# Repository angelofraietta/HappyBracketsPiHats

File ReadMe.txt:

Please quote for 100 units of these assembled.
The Bill of Materials is in the XML file

Note that the 2x20 Header is mounted on the bottom of the page, as shown in the images

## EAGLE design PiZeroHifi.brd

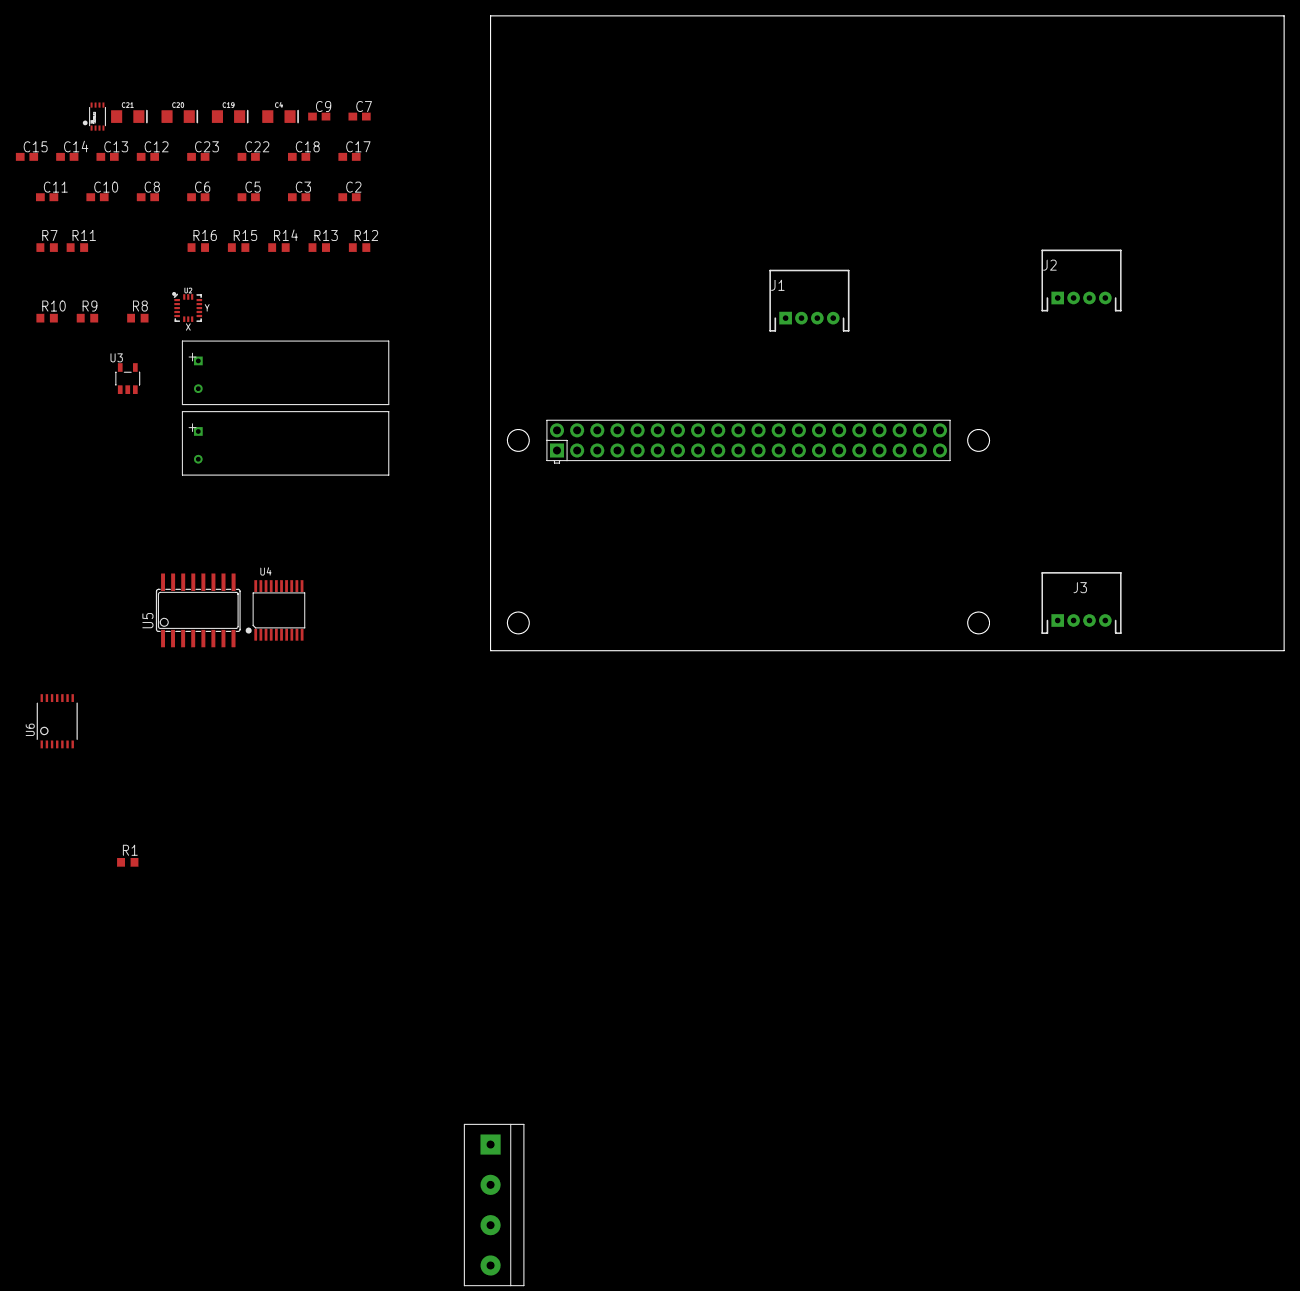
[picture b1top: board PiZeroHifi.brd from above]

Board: 2 copper layers, 100.0 x 80.0 mm, 45 parts (0 on the bottom side), 44 nets, no tracks yet.

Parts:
C1, C16: 1500uF; CAP8MMX3.5MMX20MM
C2, C10: 2.2nF; C0603
C3, C5, C11, C17, C18, C22, C23: 0.1uF; C0603
C4, C19, C20, C21: 10uF; EIA3216
C6, C8: 2.2uF; C0603
C7, C9, C13, C14, C15: 1uF; C0603
C12: 470p; C0603
CON1: RPI-ZEROPI-ZERO-THRUHOLE; RASPBERRYPI_ZERO_THRUHOLE
CON3: Audio Out; TERM-4P-SIDE-5.08MM
J1, J2, J3: GROVEGROVE-HORIZONTAL; JST-4-PTH
R1, R12, R13, R15: 10K; R0603
R7, R14, R16: 1K; R0603
R8, R9: 143K; R0603
R10, R11: 470; R0603
U1: TXS0102; VFSOP-8
U2: LSM6DS33; LGA-16-3X3
U3: TC1014-3.3V; GHI-IC_SOT23-5(MICROCHIP)
U4: PCM5101A; TSSOP20-0.65-6.5X4.4MM
U5: PAM8403; SOP-16
U6: TXB0104PWR; TSSOP14

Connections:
+3V3: C3.1, C17.2, C19.+, CON1.1, CON1.17, U1.P$3, U2.1, U2.4, U2.5, U2.16, U4.17, U4.20, U6.1
+5V: C1.P$1, C13.1, C14.1, C15.1, C16.P$1, CON1.2, CON1.4, J1.3, J2.3, J3.3, R16.2, U1.P$7, U3.1, U3.3, U5.4, U5.6, U5.13, U6.14
/MUTE: CON1.36, R12.2, R13.2
ACCEL_INT_1: CON1.11, U2.6
ACCEL_INT_2: CON1.13, U2.7
AN3V3: C4.+, C5.2, C21.+, C22.2, U3.5, U4.1, U4.8
GND: C1.P$2, C2.2, C3.2, C4.-, C5.1, C6.2, C10.2, C11.2, C12.1, C13.2, C14.2, C15.2, C16.P$2, C17.1, C18.2, C19.-, C20.-, C21.-, C22.1, C23.1, CON1.6, CON1.9, CON1.14, CON1.20, CON1.25, CON1.30, CON1.34, CON1.39, J1.4, J2.4, J3.4, R1.1, R7.2, R14.2, R15.1, U1.P$2, U2.8, U2.9, U2.10, U2.11, U2.12, U2.13, U2.15, U3.2, U4.3, U4.9, U4.10, U4.11, U4.12, U4.16, U4.19, U5.2, U5.9, U5.11, U5.15, U6.7
GPI022-OUT: J2.2, U6.11
GPIO21: CON1.29, U6.5
GPIO21-OUT: J2.1, U6.10
GPIO22: CON1.31, U6.4
GPIO23: CON1.33, U6.3
GPIO23-OUT: J1.1, U6.12
GPIO25: CON1.37, U6.2
GPIO25-OUT: J1.2, U6.13
unnamed: C8.1, U4.2
unnamed: C8.2, U4.4
unnamed: C6.1, U4.5
unnamed: C18.1, C20.+, U4.18
unnamed: R10.1, U4.6
unnamed: R11.1, U4.7
unnamed: C7.2, R8.1
unnamed: C9.1, C10.1, R11.2, R14.1
unnamed: C2.1, C7.1, R7.1, R10.2
unnamed: C9.2, R9.1
unnamed: R8.2, U5.7
unnamed: R9.2, U5.10
unnamed: C12.2, U3.4
unnamed: CON3.P$1, U5.1
unnamed: CON3.P$2, U5.3
unnamed: CON3.P$3, U5.14
unnamed: CON3.P$4, U5.16
unnamed: C11.1, U5.8
unnamed: R12.1, U5.12
unnamed: R13.1, U5.5
unnamed: C23.2, R15.2, R16.1, U1.P$6
OE: CON1.38, R1.2, U6.8
PCM_CLK: CON1.12, U4.13
PCM_DOUT: CON1.40, U4.14
PCM_FS: CON1.35, U4.15
SCL: CON1.5, U1.P$4, U2.2
SCL_OUT: J3.1, U1.P$1
SDA: CON1.3, U1.P$5, U2.3
SDA_OUT: J3.2, U1.P$8

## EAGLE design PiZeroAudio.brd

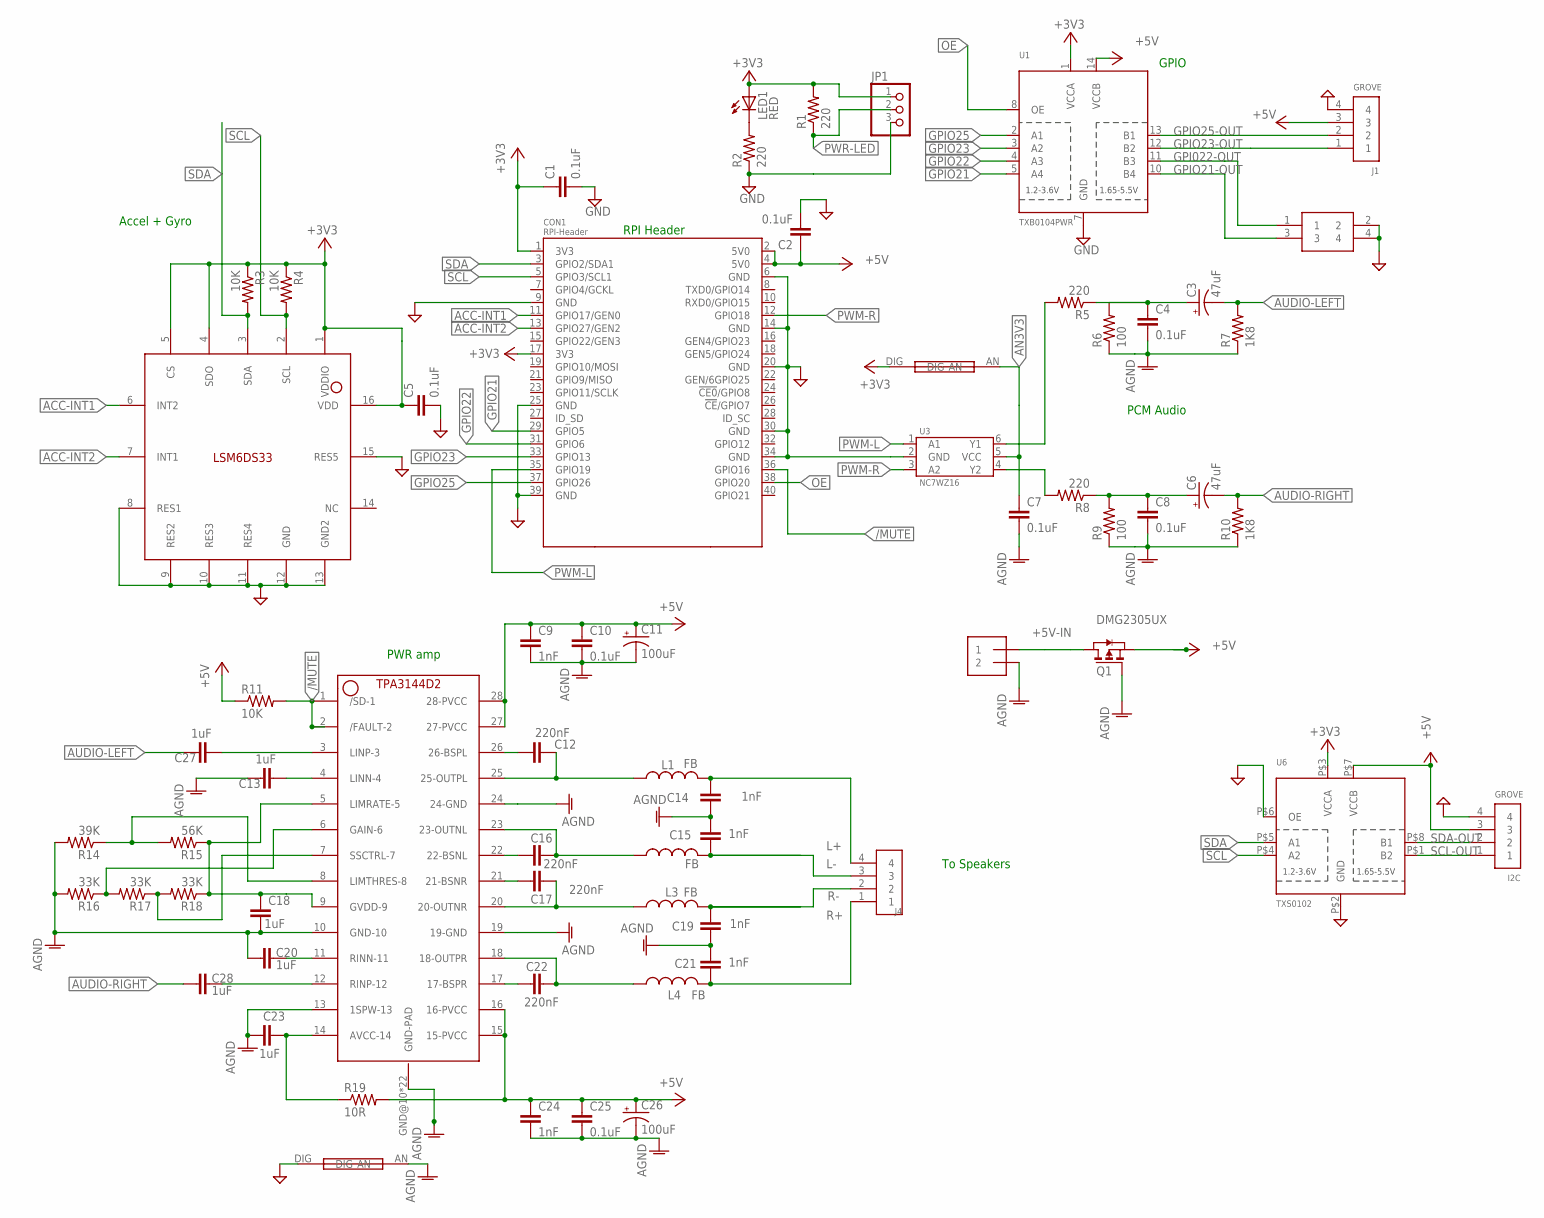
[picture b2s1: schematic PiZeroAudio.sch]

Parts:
C1, C2, C4, C5, C7, C8, C10, C25: 0.1uF; C0603
C3, C6: 47uF; EIA3216
C9, C14, C15, C19, C21, C24: 1nF; C0603
C11, C26: 100uF; EIA3216
C12, C16, C17, C22: 220nF; C0603
C13, C18, C20, C23, C27, C28: 1uF; C0603
CON1: RPI-Header; RASPBERRYPI_BASTELSTUBE_V13_RASPI_BOARD_B+_FULL
I2C: GROVE; JST-PH4
J1: GROVE; JST-PH4
J2: 2X2HEADER; 2X2
J3: 2X1-LOCKING; 22-23-2021
J4: 4X1-LOCKING; 22-23-2041
JP1: Header 1x3; 1X03
L1, L2, L3, L4: FB; L0806
LED1: RED; CHIP-LED0805
Q1: DMG2305UX; SOT23
R1, R2, R5, R8: 220; R0603
R3, R4, R11: 10K; R0603
R6, R9: 100; R0603
R7, R10: 1K8; R0603
R14: 39K; R0603
R15: 56K; R0603
R16, R17, R18: 33K; R0603
R19: 10R; R0603
SH1, SH2: SHORT
U1: TXB0104PWR; TSSOP14
U2: LSM6DS33; LGA-16-3X3
U3: NC7WZ16; SC-70-6
U5: TPA3144D2PWPR; HTSSOP28
U6: TXS0102; VFSOP-8

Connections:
+3V3: C1.1, C5.1, CON1.1 (3V3), CON1.17 (3V3), JP1.1, LED1.A, R1.2, R3.1, R4.1, SH1.DIG, U1.1 (VCCA), U2.1 (VDDIO), U2.4 (SDO), U2.5 (CS), U2.16 (VDD), U6.P$3 (VCCA)
+5V: C2.1, C9.1, C10.1, C11.+, C24.1, C25.1, C26.+, CON1.2 (5V0), CON1.4 (5V0), I2C.3, J1.3, Q1.S, R11.1, R19.2, U1.14 (VCCB), U5.15 (15-PVCC), U5.16 (16-PVCC), U5.27 (27-PVCC), U5.28 (28-PVCC), U6.P$7 (VCCB)
+5V-IN: J3.1, Q1.D
/MUTE: CON1.36 (GPIO16), R11.2, U5.1 (/SD-1), U5.2 (/FAULT-2)
ACC-INT1: CON1.11 (GPIO17/GEN0), U2.6 (INT2)
ACC-INT2: CON1.13 (GPIO27/GEN2), U2.7 (INT1)
AGND: C4.2, C7.2, C8.2, C9.2, C10.2, C11.-, C13.2, C14.2, C15.1, C18.2, C19.2, C20.2, C21.1, C23.2, C24.2, C25.2, C26.-, J3.2, Q1.G, R6.1, R7.1, R9.1, R10.1, R14.2, R16.2, SH2.AN, U5.10 (GND-10), U5.13 (1SPW-13), U5.19 (19-GND), U5.24 (24-GND), U5.GND@10 (GND-PAD), U5.GND@11 (GND-PAD), U5.GND@12 (GND-PAD), U5.GND@13 (GND-PAD), U5.GND@14 (GND-PAD), U5.GND@15 (GND-PAD), U5.GND@16 (GND-PAD), U5.GND@17 (GND-PAD), U5.GND@18 (GND-PAD), U5.GND@19 (GND-PAD), U5.GND@20 (GND-PAD), U5.GND@21 (GND-PAD), U5.GND@22 (GND-PAD), U5.GND@23 (GND-PAD), U5.GND@24 (GND-PAD), U5.GND@25 (GND-PAD), U5.GND@26 (GND-PAD), U5.GND@27 (GND-PAD), U5.GND@28 (GND-PAD), U5.GND@29 (GND-PAD), U5.GND@30 (GND-PAD), U5.GND@PAD (GND-PAD)
AN3V3: C7.1, SH1.AN, U3.5 (VCC)
AUDIO-LEFT: C3.-, C27.2, R7.2
AUDIO-RIGHT: C6.-, C28.2, R10.2
GND: C1.2, C2.2, C5.2, CON1.6 (GND), CON1.9 (GND), CON1.14 (GND), CON1.20 (GND), CON1.25 (GND), CON1.30 (GND), CON1.34 (GND), CON1.39 (GND), I2C.4, J1.4, J2.2, J2.4, JP1.3, R2.1, SH2.DIG, U1.7 (GND), U2.8 (RES1), U2.9 (RES2), U2.10 (RES3), U2.11 (RES4), U2.12 (GND), U2.13 (GND2), U2.15 (RES5), U3.2 (GND), U6.P$2 (GND), U6.P$6 (OE)
GPI022-OUT: J2.1, U1.11 (B3)
GPIO21: CON1.29 (GPIO5), U1.5 (A4)
GPIO21-OUT: J2.3, U1.10 (B4)
GPIO22: CON1.31 (GPIO6), U1.4 (A3)
GPIO23: CON1.33 (GPIO13), U1.3 (A2)
GPIO23-OUT: J1.1, U1.12 (B2)
GPIO25: CON1.37 (GPIO26), U1.2 (A1)
GPIO25-OUT: J1.2, U1.13 (B1)
L+: C14.1, J4.4, L1.2
L-: C15.2, J4.3, L2.2
unnamed: C3.+, C4.1, R5.1, R6.2
unnamed: R5.2, U3.6 (Y1)
unnamed: R8.2, U3.4 (Y2)
unnamed: C6.+, C8.1, R8.1, R9.2
unnamed: C27.1, U5.3 (LINP-3)
unnamed: LED1.C, R2.2
unnamed: C13.1, U5.4 (LINN-4)
unnamed: C20.1, U5.11 (RINN-11)
unnamed: C23.1, R19.1, U5.14 (AVCC-14)
unnamed: C22.2, U5.17 (17-BSPR)
unnamed: C28.1, U5.12 (RINP-12)
unnamed: C17.2, U5.21 (21-BSNR)
unnamed: C16.2, U5.22 (22-BSNL)
unnamed: C12.2, U5.26 (26-BSPL)
unnamed: C12.1, L1.1, U5.25 (25-OUTPL)
unnamed: C16.1, L2.1, U5.23 (23-OUTNL)
unnamed: C17.1, L3.1, U5.20 (20-OUTNR)
unnamed: C22.1, L4.1, U5.18 (18-OUTPR)
unnamed: R16.1, R17.2, U5.6 (GAIN-6)
unnamed: R17.1, R18.2, U5.7 (SSCTRL-7)
unnamed: R14.1, R15.2, U5.8 (LIMTHRES-8)
unnamed: C18.1, R15.1, R18.1, U5.5 (LIMRATE-5), U5.9 (GVDD-9)
OE: CON1.38 (GPIO20), U1.8 (OE)
PWM-L: CON1.35 (GPIO19), U3.1 (A1)
PWM-R: CON1.12 (GPIO18), U3.3 (A2)
PWR-LED: JP1.2, R1.1
R+: C21.2, J4.1, L4.2
R-: C19.1, J4.2, L3.2
SCL: CON1.5 (GPIO3/SCL1), R4.2, U2.2 (SCL), U6.P$4 (A2)
SCL-OUT: I2C.1, U6.P$1 (B2)
SDA: CON1.3 (GPIO2/SDA1), R3.2, U2.3 (SDA), U6.P$5 (A1)
SDA-OUT: I2C.2, U6.P$8 (B1)

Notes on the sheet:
Accel + Gyro
GPIO
PCM Audio
PWR amp
RPI Header
To Speakers

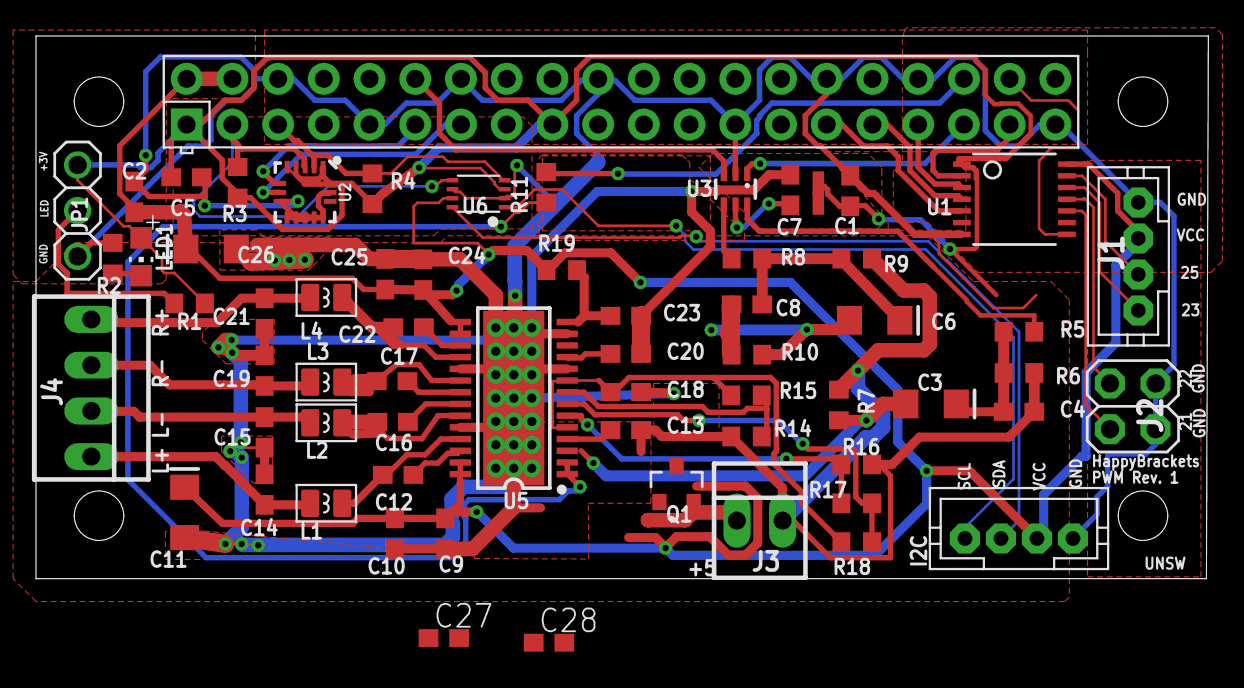
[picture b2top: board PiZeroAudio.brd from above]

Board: 2 copper layers, 65.1 x 30.2 mm, 65 parts (0 on the bottom side), 53 nets.

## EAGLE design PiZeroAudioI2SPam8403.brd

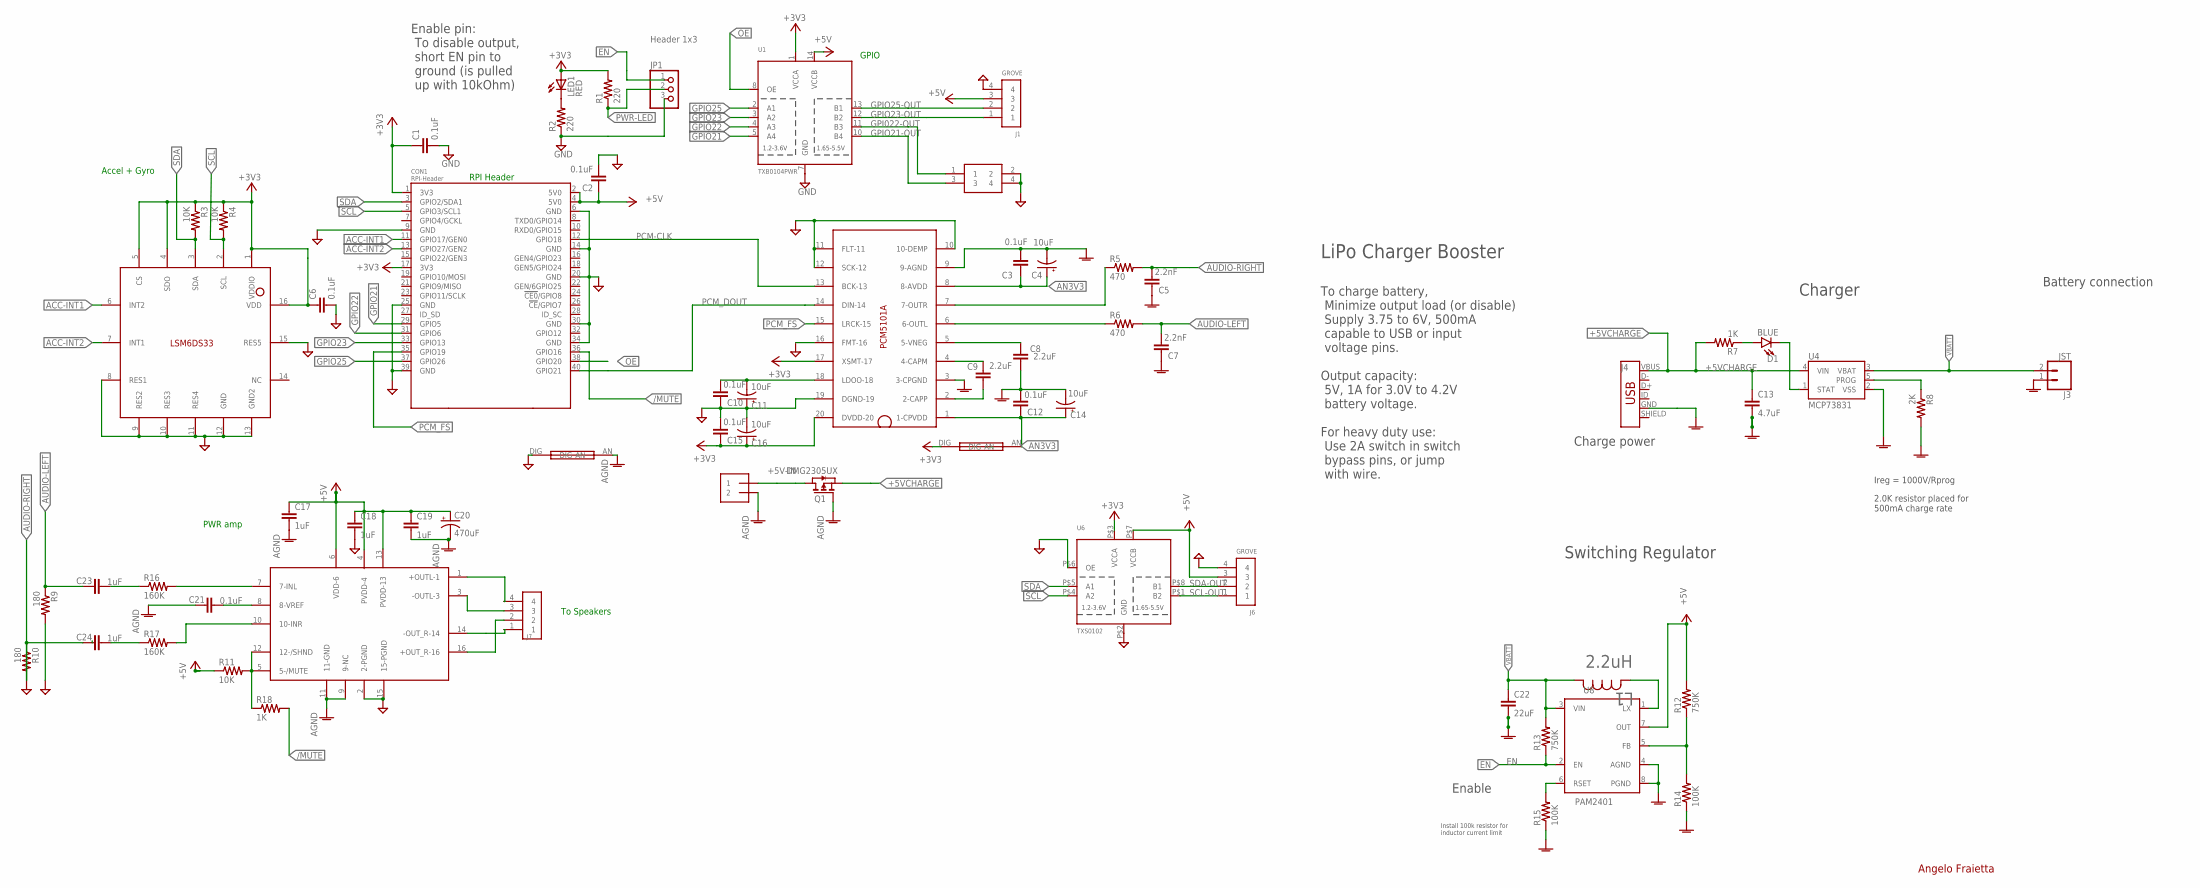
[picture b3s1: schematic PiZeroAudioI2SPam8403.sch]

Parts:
C1, C2, C3, C6, C10, C12, C15, C21: 0.1uF; C0603; MPN MC0603F104Z500CT
C4, C11, C14, C16: 10uF; EIA3216; MPN F931C106MAA
C5, C7: 2.2nF; C0603
C8, C9: 2.2uF; C0603; MPN TMK107ABJ225KA-T
C13: 4.7uF; C0603
C17, C18, C19: 1uF; C0603
C20: 470uF; EIA7343; MPN 293D477X9010E2TE3
C22: 22uF; C0603; MPN GRM188R61A226ME15D
C23, C24: 1uF; C0603; MPN MC0603F104Z500CT
CON1: RPI-Header; RASPBERRYPI_BASTELSTUBE_V13_RASPI_BOARD_B+_FULL
D1: BLUE; LED-0603
J1, J6: GROVE; JST-PH4
J2: 2X2HEADER; 2X2
J3: JST; JST-2-SMD; MPN S2B-PH-SM4-TB(LF)(SN)
J4: AMP FCI 10103594-0001LF; USB-MICROB-PTH; MPN 10103594-0001LF
J5: 2X1-LOCKING; 22-23-2021
J7: 4X1-LOCKING; 22-23-2041
JP1: Header 1x3; 1X03
L1: 2.2uH; IND_IFSC_1515AH; MPN IFSC1515AHER2R2M01
LED1: RED; CHIP-LED0805
Q1: DMG2305UX; SOT23; MPN DMG2305UX-7
R1, R2: 220; R0603; MPN RC0603FR-07220RL
R3, R4, R11: 10K; R0603; MPN RC0603FR-0710KL
R5, R6: 470; R0603; MPN ERJ3EKF4700V
R7: 1K; R0603; MPN CRCW06031K00FKEA
R8: 2K; R0603
R9, R10: 180; R0603; MPN ERJ3EKF4700V
R12, R13: 750K; R0603; MPN CRCW0603750KFKEA
R14, R15: 100K; R0603; MPN ERJ-3EKF1003V
R16, R17: 160K; R0603; MPN ERJ3EKF4700V
R18: 1K; R0603; MPN RC0603FR-0710KL
SH1, SH2: SHORT
U1: TXB0104PWR; TSSOP14; MPN TXB0104PWR
U2: LSM6DS33; LGA-16-3X3; MPN LSM6DS33TR
U3: PCM5101A; TSSOP20-0.65-6.5X4.4MM; MPN PCM5101AQPWRQ1
U4: MCP73831; SOT23-5; MPN MCP73831T-2ACI/OT
U6: TXS0102; VFSOP-8
U7: PAM8403; SOP-16
U8: PAM2401; MSOP8

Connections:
+3V3: C1.1, C6.1, C15.2, C16.+, CON1.1 (3V3), CON1.17 (3V3), LED1.A, R1.2, R3.1, R4.1, SH1.DIG, U1.1 (VCCA), U2.1 (VDDIO), U2.4 (SDO), U2.5 (CS), U2.16 (VDD), U3.17 (XSMT-17), U3.20 (DVDD-20), U6.P$3 (VCCA)
+5V: C2.1, C17.1, C18.1, C19.1, C20.+, CON1.2 (5V0), CON1.4 (5V0), J1.3, J6.3, R11.1, R12.2, U1.14 (VCCB), U6.P$7 (VCCB), U7.4 (PVDD-4), U7.6 (VDD-6), U7.13 (PVDD-13), U8.7 (OUT)
+5V-IN: J5.1, Q1.D
+5VCHARGE: C13.1, J4.VBUS, Q1.S, R7.2, U4.4 (VIN)
/MUTE: CON1.36 (GPIO16), R11.2, R18.1, R18.2, U7.5 (5-/MUTE), U7.12 (12-/SHND)
ACC-INT1: CON1.11 (GPIO17/GEN0), U2.6 (INT2)
ACC-INT2: CON1.13 (GPIO27/GEN2), U2.7 (INT1)
AGND: C3.1, C4.-, C5.2, C7.2, C8.2, C12.1, C13.2, C14.-, C17.2, C19.2, C20.-, C21.2, C22.2, J3.1 (2), J4.GND, J5.2, Q1.G, R8.2, R14.1, R15.1, SH2.AN, U3.3 (3-CPGND), U3.9 (9-AGND), U4.2 (VSS), U7.9 (9-NC), U7.11 (11-GND), U8.4 (AGND), U8.8 (PGND)
AN3V3: C3.2, C4.+, C12.2, C14.+, SH1.AN, U3.1 (1-CPVDD), U3.8 (8-AVDD)
AUDIO-LEFT: C7.1, C23.2, R6.2, R9.1
AUDIO-RIGHT: C5.1, R5.2, R10.1
EN: JP1.1, R13.1, U8.2 (EN)
GND: C1.2, C2.2, C6.2, C10.2, C11.+, C15.1, C16.-, C18.2, C24.2, CON1.6 (GND), CON1.9 (GND), CON1.14 (GND), CON1.20 (GND), CON1.25 (GND), CON1.30 (GND), CON1.34 (GND), CON1.39 (GND), J1.4, J2.2, J2.4, J6.4, JP1.3, R2.1, R9.2, R10.2, SH2.DIG, U1.7 (GND), U2.8 (RES1), U2.9 (RES2), U2.10 (RES3), U2.11 (RES4), U2.12 (GND), U2.13 (GND2), U2.15 (RES5), U3.10 (10-DEMP), U3.11 (FLT-11), U3.12 (SCK-12), U3.16 (FMT-16), U3.19 (DGND-19), U6.P$2 (GND), U6.P$6 (OE), U7.2 (2-PGND), U7.15 (15-PGND)
GPI022-OUT: J2.1, U1.11 (B3)
GPIO21: CON1.29 (GPIO5), U1.5 (A4)
GPIO21-OUT: J2.3, U1.10 (B4)
GPIO22: CON1.31 (GPIO6), U1.4 (A3)
GPIO23: CON1.33 (GPIO13), U1.3 (A2)
GPIO23-OUT: J1.1, U1.12 (B2)
GPIO25: CON1.37 (GPIO26), U1.2 (A1)
GPIO25-OUT: J1.2, U1.13 (B1)
L+: J7.4, U7.1 (+OUTL-1)
L-: J7.3, U7.3 (-OUTL-3)
unnamed: R5.1, U3.7 (7-OUTR)
unnamed: C8.1, U3.5 (5-VNEG)
unnamed: C9.1, U3.4 (4-CAPM)
unnamed: C9.2, U3.2 (2-CAPP)
unnamed: C24.1, R17.1
unnamed: LED1.C, R2.2
unnamed: C21.1, U7.8 (8-VREF)
unnamed: R16.2, U7.7 (7-INL)
unnamed: R17.2, U7.10 (10-INR)
unnamed: R6.1, U3.6 (6-OUTL)
unnamed: C10.1, C11.-, U3.18 (LDOO-18)
unnamed: C23.1, R16.1
unnamed: R8.1, U4.5 (PROG)
unnamed: D1.C, U4.1 (STAT)
unnamed: R12.1, R14.2, U8.5 (FB)
unnamed: L1.2, U8.1 (LX)
unnamed: R15.2, U8.6 (RSET)
unnamed: D1.A, R7.1
OE: CON1.38 (GPIO20), U1.8 (OE)
PCM-CLK: CON1.12 (GPIO18), U3.13 (BCK-13)
PCM_DOUT: CON1.40 (GPIO21), U3.14 (DIN-14)
PCM_FS: CON1.35 (GPIO19), U3.15 (LRCK-15)
PWR-LED: JP1.2, R1.1
R+: J7.2, U7.16 (+OUT_R-16)
R-: J7.1, U7.14 (-OUT_R-14)
SCL: CON1.5 (GPIO3/SCL1), R4.2, U2.2 (SCL), U6.P$4 (A2)
SCL-OUT: J6.1, U6.P$1 (B2)
SDA: CON1.3 (GPIO2/SDA1), R3.2, U2.3 (SDA), U6.P$5 (A1)
SDA-OUT: J6.2, U6.P$8 (B1)
VBATT: C22.1, J3.2 (1), L1.1, R13.2, U4.3 (VBAT), U8.3 (VIN)

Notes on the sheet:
Accel + Gyro
GPIO
PWR amp
RPI Header
To Speakers
Charger
Switching Regulator
Angelo Fraietta
2.0K resistor placed for 500mA charge rate
Ireg = 1000V/Rprog
To charge battery, Minimize output load (or disable) Supply 3.75 to 6V, 500mA capable to USB or input voltage pins.
Install 100k resistor for inductor current limit
LiPo Charger Booster
Output capacity: 5V, 1A for 3.0V to 4.2V battery voltage.
Enable pin: To disable output, short EN pin to ground (is pulled up with 10kOhm)
Enable
Charge power
Battery connection
For heavy duty use: Use 2A switch in switch bypass pins, or jump with wire.

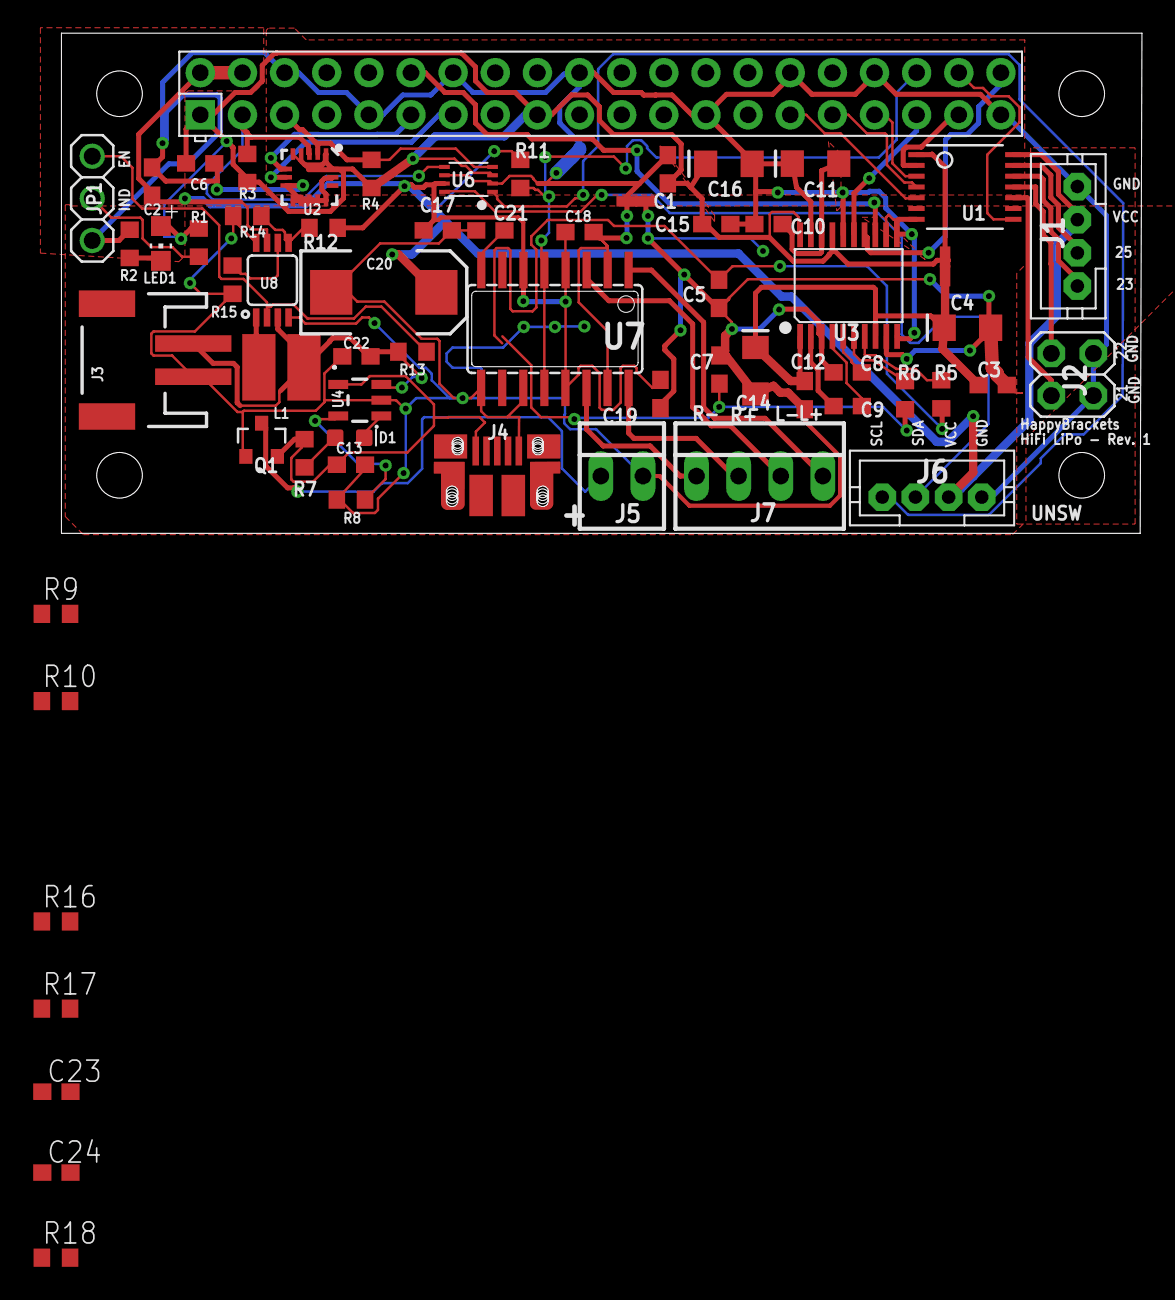
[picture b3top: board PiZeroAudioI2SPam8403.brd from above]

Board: 2 copper layers, 65.1 x 30.2 mm, 64 parts (0 on the bottom side), 53 nets.

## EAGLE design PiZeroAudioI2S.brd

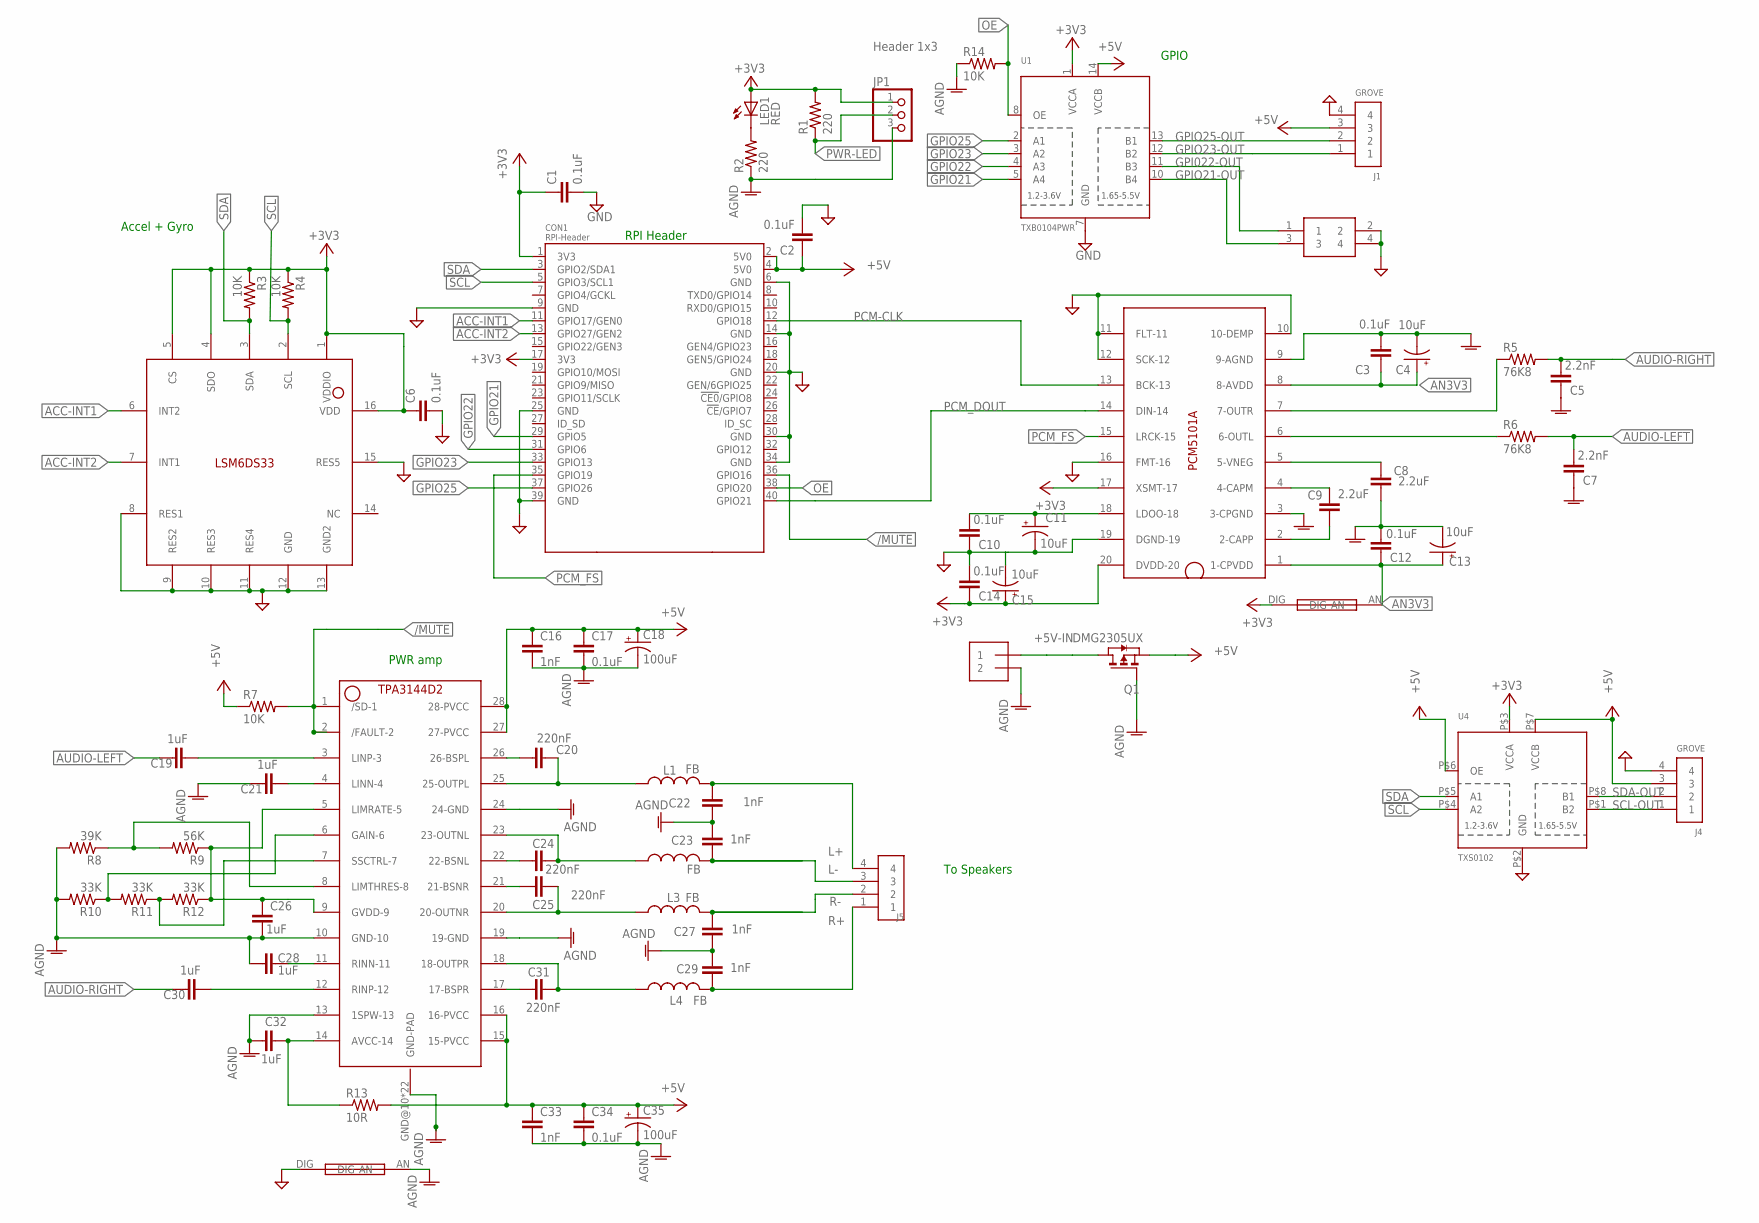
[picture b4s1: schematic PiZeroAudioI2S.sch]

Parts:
C1, C2, C3, C6, C10, C12, C14, C17, C34: 0.1uF; C0603
C4, C11, C13, C15: 10uF; EIA3216; MPN F931C106MAA
C5, C7: 2.2nF; C0603; MPN 0603B222K500CT
C8, C9: 2.2uF; C0603; MPN C0603C225K8PACTU
C16, C22, C23, C27, C29, C33: 1nF; C0603; MPN 06035C102KAT2A
C18, C35: 100uF; EIA3216; MPN TLJA107M010R1400
C19, C21, C26, C28, C30, C32: 1uF; C0603
C20, C24, C25, C31: 220nF; C0603; MPN EMK107B7224KA-T
CON1: RPI-Header; RASPBERRYPI_BASTELSTUBE_V13_RASPI_BOARD_B+_FULL
J1, J4: GROVE; JST-PH4
J2: 2X2HEADER; 2X2
J3: 2X1-LOCKING; 22-23-2021; MPN 22-23-2021
J5: 4X1-LOCKING; 22-23-2041; MPN 22-23-2041
JP1: Header 1x3; 1X03
L1, L2, L3, L4: FB; L0806
LED1: RED; CHIP-LED0805
Q1: DMG2305UX; SOT23; MPN DMG2305UX-7
R1, R2: 220; R0603
R3, R4, R7, R14: 10K; R0603; MPN RC0603FR-0710KL
R5, R6: 76K8; R0603; MPN RMCF0603FT76K8
R8: 39K; R0603; MPN RC0603FR-0739KL
R9: 56K; R0603; MPN CRCW060356K0FKEA.
R10, R11, R12: 33K; R0603; MPN MCMR06X3302FTL
R13: 10R; R0603
SH1, SH2: SHORT
U1: TXB0104PWR; TSSOP14; MPN TXB0104PWR
U2: LSM6DS33; LGA-16-3X3; MPN LSM6DS33TR
U3: PCM5101A; TSSOP20-0.65-6.5X4.4MM; MPN PCM5101AQPWRQ1
U4: TXS0102; VFSOP-8
U5: TPA3144D2PWPR; HTSSOP28

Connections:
+5V-IN: J3.1, Q1.D
/MUTE: CON1.36 (GPIO16), R7.2, U5.1 (/SD-1), U5.2 (/FAULT-2)
ACC-INT1: CON1.11 (GPIO17/GEN0), U2.6 (INT2)
ACC-INT2: CON1.13 (GPIO27/GEN2), U2.7 (INT1)
AGND: C3.1, C4.-, C5.2, C7.2, C8.2, C12.1, C13.-, C16.2, C17.2, C18.-, C21.2, C22.2, C23.1, C26.2, C27.2, C28.2, C29.1, C32.2, C33.2, C34.2, C35.-, J3.2, JP1.3, Q1.G, R2.1, R8.2, R10.2, R14.1, SH2.AN, U3.3 (3-CPGND), U3.9 (9-AGND), U5.10 (GND-10), U5.13 (1SPW-13), U5.19 (19-GND), U5.24 (24-GND), U5.GND@10 (GND-PAD), U5.GND@11 (GND-PAD), U5.GND@12 (GND-PAD), U5.GND@13 (GND-PAD), U5.GND@14 (GND-PAD), U5.GND@15 (GND-PAD), U5.GND@16 (GND-PAD), U5.GND@17 (GND-PAD), U5.GND@18 (GND-PAD), U5.GND@19 (GND-PAD), U5.GND@20 (GND-PAD), U5.GND@21 (GND-PAD), U5.GND@22 (GND-PAD), U5.GND@23 (GND-PAD), U5.GND@24 (GND-PAD), U5.GND@25 (GND-PAD), U5.GND@26 (GND-PAD), U5.GND@27 (GND-PAD), U5.GND@28 (GND-PAD), U5.GND@29 (GND-PAD), U5.GND@30 (GND-PAD), U5.GND@PAD (GND-PAD)
AN3V3: C3.2, C4.+, C12.2, C13.+, SH1.AN, U3.1 (1-CPVDD), U3.8 (8-AVDD)
AUDIO-LEFT: C7.1, C19.2, R6.2
AUDIO-RIGHT: C5.1, C30.2, R5.2
GND: C1.2, C2.2, C6.2, C10.2, C11.-, C14.1, C15.-, CON1.6 (GND), CON1.9 (GND), CON1.14 (GND), CON1.20 (GND), CON1.25 (GND), CON1.30 (GND), CON1.34 (GND), CON1.39 (GND), J1.4, J2.2, J2.4, J4.4, SH2.DIG, U1.7 (GND), U2.8 (RES1), U2.9 (RES2), U2.10 (RES3), U2.11 (RES4), U2.12 (GND), U2.13 (GND2), U2.15 (RES5), U3.10 (10-DEMP), U3.11 (FLT-11), U3.12 (SCK-12), U3.16 (FMT-16), U3.19 (DGND-19), U4.P$2 (GND)
GPI022-OUT: J2.1, U1.11 (B3)
GPIO21: CON1.29 (GPIO5), U1.5 (A4)
GPIO21-OUT: J2.3, U1.10 (B4)
GPIO22: CON1.31 (GPIO6), U1.4 (A3)
GPIO23: CON1.33 (GPIO13), U1.3 (A2)
GPIO23-OUT: J1.1, U1.12 (B2)
GPIO25: CON1.37 (GPIO26), U1.2 (A1)
GPIO25-OUT: J1.2, U1.13 (B1)
L+: C22.1, J5.4, L1.2
L-: C23.2, J5.3, L2.2
unnamed: R5.1, U3.7 (7-OUTR)
unnamed: C8.1, U3.5 (5-VNEG)
unnamed: C9.1, U3.4 (4-CAPM)
unnamed: C9.2, U3.2 (2-CAPP)
unnamed: LED1.C, R2.2
unnamed: C21.1, U5.4 (LINN-4)
unnamed: C28.1, U5.11 (RINN-11)
unnamed: C32.1, R13.1, U5.14 (AVCC-14)
unnamed: C31.2, U5.17 (17-BSPR)
unnamed: R6.1, U3.6 (6-OUTL)
unnamed: C10.1, C11.+, U3.18 (LDOO-18)
unnamed: C25.2, U5.21 (21-BSNR)
unnamed: C19.1, U5.3 (LINP-3)
unnamed: C30.1, U5.12 (RINP-12)
unnamed: C24.2, U5.22 (22-BSNL)
unnamed: C20.2, U5.26 (26-BSPL)
unnamed: C20.1, L1.1, U5.25 (25-OUTPL)
unnamed: C24.1, L2.1, U5.23 (23-OUTNL)
unnamed: C25.1, L3.1, U5.20 (20-OUTNR)
unnamed: C31.1, L4.1, U5.18 (18-OUTPR)
unnamed: R10.1, R11.2, U5.6 (GAIN-6)
unnamed: R11.1, R12.2, U5.7 (SSCTRL-7)
unnamed: R8.1, R9.2, U5.8 (LIMTHRES-8)
unnamed: C26.1, R9.1, R12.1, U5.5 (LIMRATE-5), U5.9 (GVDD-9)
OE: CON1.38 (GPIO20), R14.2, U1.8 (OE)
PCM-CLK: CON1.12 (GPIO18), U3.13 (BCK-13)
PCM_DOUT: CON1.40 (GPIO21), U3.14 (DIN-14)
PCM_FS: CON1.35 (GPIO19), U3.15 (LRCK-15)
PWR-LED: JP1.2, R1.1
R+: C29.2, J5.1, L4.2
R-: C27.1, J5.2, L3.2
SCL: CON1.5 (GPIO3/SCL1), R4.2, U2.2 (SCL), U4.P$4 (A2)
SCL-OUT: J4.1, U4.P$1 (B2)
SDA: CON1.3 (GPIO2/SDA1), R3.2, U2.3 (SDA), U4.P$5 (A1)
SDA-OUT: J4.2, U4.P$8 (B1)

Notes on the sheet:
Accel + Gyro
GPIO
PWR amp
RPI Header
To Speakers

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
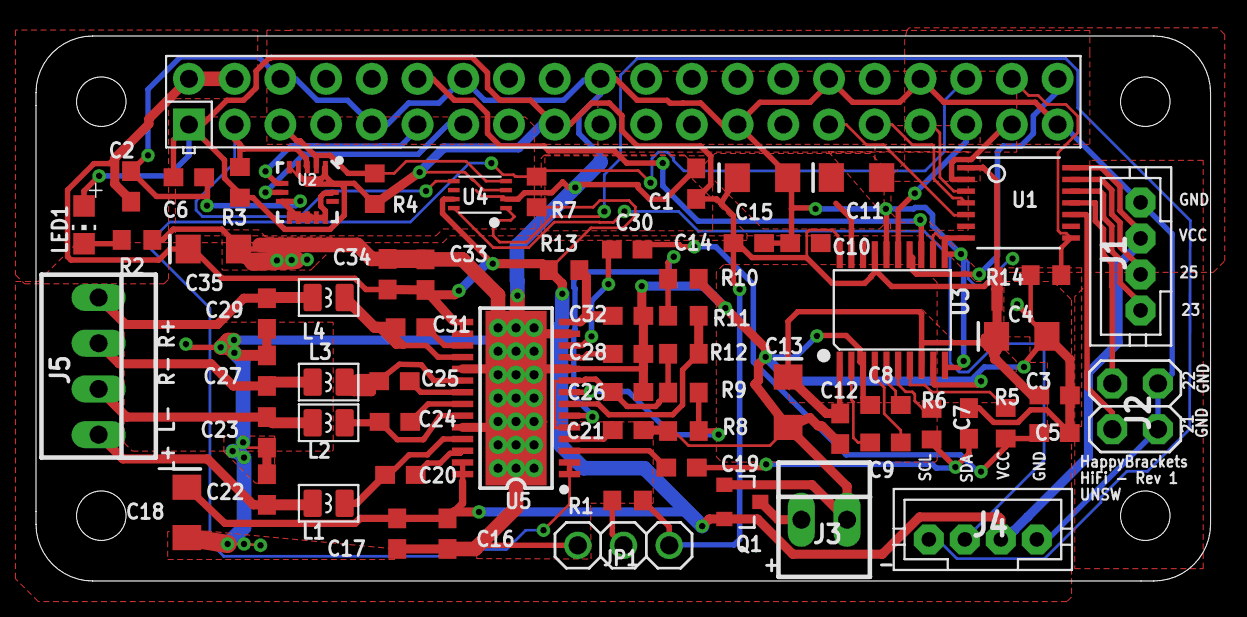
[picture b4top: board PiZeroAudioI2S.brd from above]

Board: 2 copper layers, 65.3 x 30.3 mm, 69 parts (0 on the bottom side), 56 nets.

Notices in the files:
parts and their libraries:
SparkFun-LED: Licensing: Creative Commons ShareAlike 4.0 International - https://creativecommons.org/licenses/by-sa/4.0
